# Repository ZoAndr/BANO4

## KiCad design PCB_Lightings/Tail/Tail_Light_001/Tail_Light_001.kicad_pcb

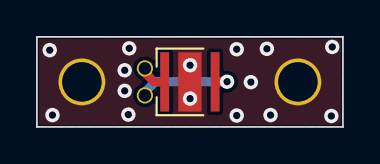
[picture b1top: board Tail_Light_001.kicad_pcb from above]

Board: 2 copper layers, 17.0 x 5.0 mm, 5 parts (0 on the bottom side), 3 nets.

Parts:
D1: LED_Cree_XHP50_6V; LED_Cree-XHP35
D2, D3: Conn_Hole_0p7; WireHole_0p7
U1, U2: Mounting_Hole_M2; Hole_screw_M2

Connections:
unnamed: D1.1 (K), D3.1
unnamed: D1.2 (A), D2.1
unnamed: D1.3 (PAD), U1.1 (Mnt), U2.1 (Mnt)

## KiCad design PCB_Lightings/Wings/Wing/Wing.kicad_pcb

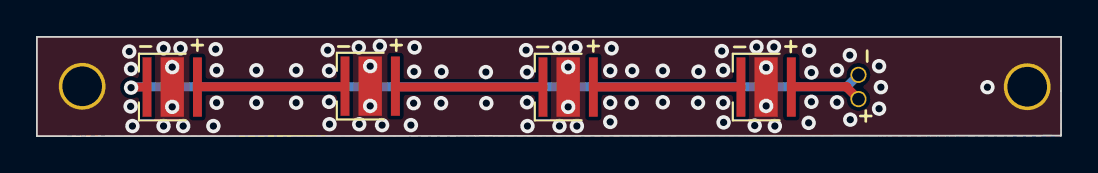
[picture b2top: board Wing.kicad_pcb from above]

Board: 2 copper layers, 56.9 x 5.5 mm, 8 parts (0 on the bottom side), 6 nets.

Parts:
D1, D2, D3, D4: LED_Cree_XHP50_6V; LED_Cree-XHP35
D5, D6: Conn_Hole_0p7; WireHole_0p7
U1, U2: Mounting_Hole_M2; Hole_screw_M2

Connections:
unnamed: D1.1 (K), D6.1
unnamed: D1.2 (A), D2.1 (K)
unnamed: D1.3 (PAD), D2.3 (PAD), D3.3 (PAD), D4.3 (PAD), U1.1 (Mnt), U2.1 (Mnt)
unnamed: D2.2 (A), D3.1 (K)
unnamed: D3.2 (A), D4.1 (K)
unnamed: D4.2 (A), D5.1

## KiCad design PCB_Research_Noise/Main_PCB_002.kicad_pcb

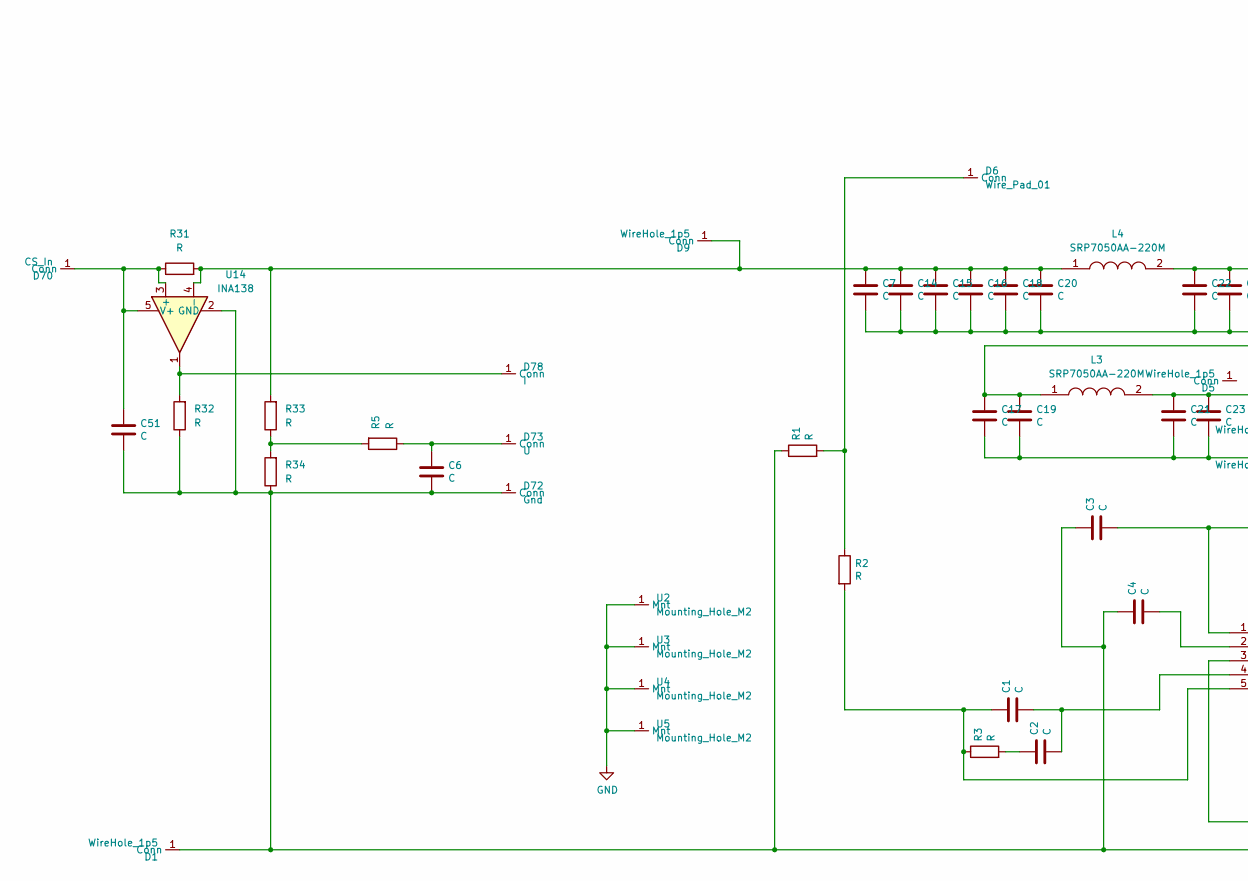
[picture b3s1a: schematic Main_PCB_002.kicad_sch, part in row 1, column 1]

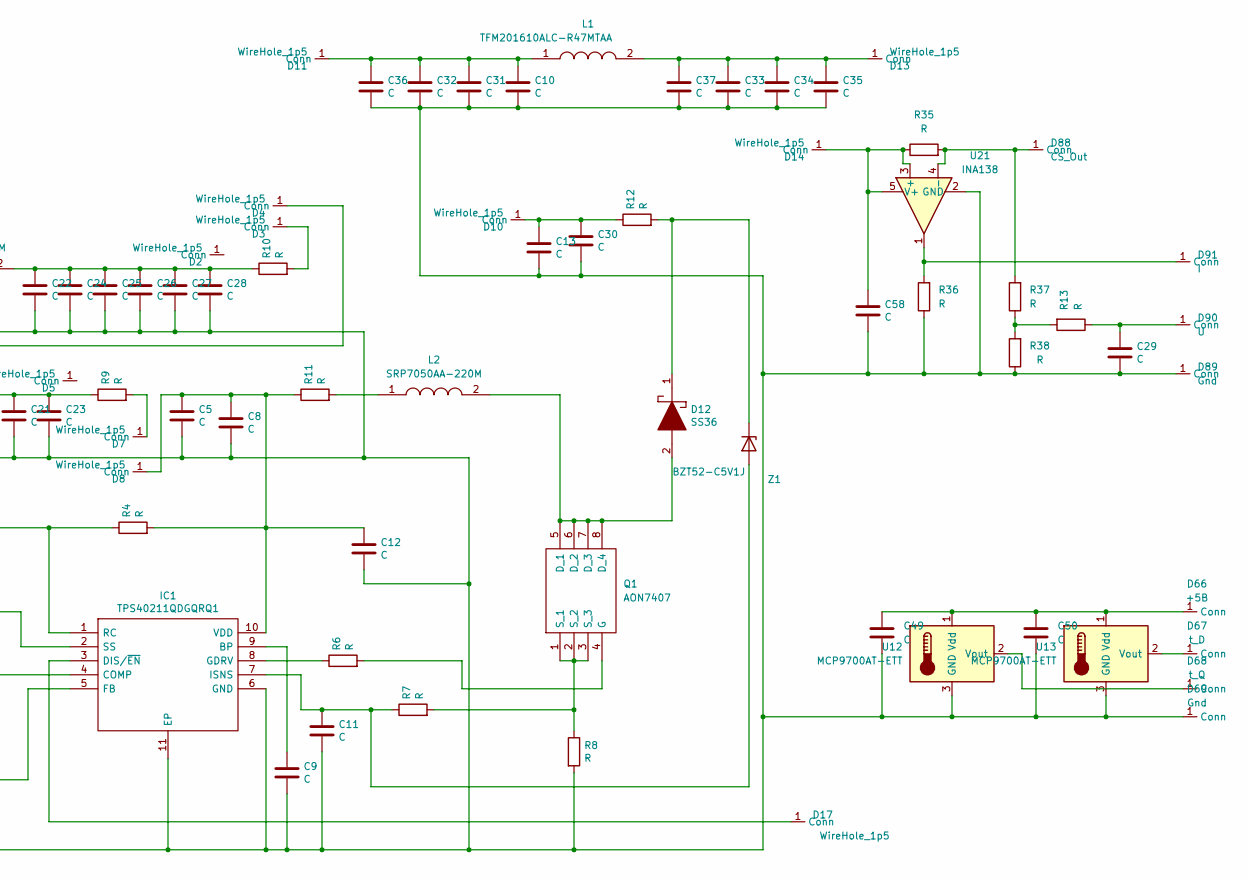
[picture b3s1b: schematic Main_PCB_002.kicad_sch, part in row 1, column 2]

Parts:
C1, C2, C3, C4, C5, C6, C8, C9, C10, C11, C14, C15, C16, C17, C18, C19, C20, C21, C22, C23, C24, C25, C26, C27, C29, C30, C31, C32, C33, C34, C35, C36, C37, C49, C50, C51, C58: C; C_0805_2012Metric_Pad1.18x1.45mm_HandSolder
C7, C12, C28: C; C_0603_1608Metric_Pad1.08x0.95mm_HandSolder
C13: C; C_1206_3216Metric_Pad1.33x1.80mm_HandSolder
D1, D2, D3, D4, D5, D7, D8, D9, D10, D11, D13, D14, D17: WireHole_1p5; WireHole_1p2
D6: Wire_Pad_01; Wire_Hole_1mm
D12: SS36; SODFL4626X120N; Manufacturer_Part_Number SS36
D66: +5B; WireHole_1p2
D67: t_D; WireHole_1p2
D68: t_Q; WireHole_1p2
D69: Gnd; WireHole_1p2
D70: CS_In; Wire_Hole_1mm
D72, D89: Gnd; Wire_Hole_1mm
D73, D90: U; Wire_Hole_1mm
D78, D91: I; Wire_Hole_1mm
D88: CS_Out; Wire_Hole_1mm
IC1: TPS40211QDGQRQ1; SOP50P490X110-11N; Manufacturer_Part_Number TPS40211QDGQRQ1; Mouser Part Number 595-TPS40211QDGQRQ1
L1: TFM201610ALC-R47MTAA; INDC2016X80N; Manufacturer_Part_Number TFM201610ALC-R47MTAA; Mouser Part Number 810-TFM201610ALCR47M
L2, L3, L4: SRP7050AA-220M; INDPM5752X300N; Manufacturer_Part_Number SRP7050AA-220M; Mouser Part Number 652-SRP7050AA-220M
Q1: AON7407; DFN_3X3_EP; Manufacturer_Part_Number AON7407
R1, R2, R3, R4, R5, R6, R7, R8, R9, R10, R11, R12, R13, R31, R32, R33, R34, R35, R36, R37, R38: R; R_0805_2012Metric_Pad1.20x1.40mm_HandSolder
U2, U3, U4, U5: Mounting_Hole_M2; Mounting_Wuerth_WA-SMST-2.7mm_H1mm_9774010951
U12, U13: MCP9700AT-ETT; SOT-23
U14, U21: INA138; SOT-23-5
Z1: BZT52-C5V1J; D_SOD-323F; Manufacturer_Part_Number BZT52-C5V1J; Mouser Part Number N/A

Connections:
GND: U2.1 (Mnt), U3.1 (Mnt), U4.1 (Mnt), U5.1 (Mnt)
unnamed: C2.1, R3.2
unnamed: C21.1, C23.1, L3.2, R9.1
unnamed: C22.1, C24.1, C25.1, C26.1, C27.1, C28.1, L4.2, R10.1
unnamed: C3.1, C4.1, C5.2, C6.2, C7.2, C8.2, C9.2, C10.2, C11.2, C12.2, C13.2, C14.2, C15.2, C16.2, C17.2, C18.2, C19.2, C20.2, C21.2, C22.2, C23.2, C24.2, C25.2, C26.2, C27.2, C28.2, C29.2, C30.2, C31.2, C32.2, C33.2, C34.2, C35.2, C36.2, C37.2, C49.2, C50.2, C51.2, C58.2, D1.1 (Conn), D69.1 (Conn), D72.1 (Conn), D89.1 (Conn), IC1.6 (GND), IC1.11 (EP), R1.1, R8.2, R32.1, R34.1, R36.1, R38.1, U12.3 (GND), U13.3 (GND), U14.2 (GND), U21.2 (GND)
unnamed: D3.1 (Conn), R10.2
unnamed: C17.1, C19.1, D4.1 (Conn), L3.1
unnamed: D6.1 (Conn), R1.2, R2.1
unnamed: D7.1 (Conn), R9.2
unnamed: C5.1, C8.1, C12.1, D8.1 (Conn), IC1.10 (VDD), R4.2, R11.1
unnamed: C7.1, C14.1, C15.1, C16.1, C18.1, C20.1, D9.1 (Conn), L4.1, R31.2, R33.2, U14.4 (-)
unnamed: C13.1, C30.1, D10.1 (Conn), R12.1
unnamed: C10.1, C31.1, C32.1, C36.1, D11.1 (Conn), L1.1
unnamed: C33.1, C34.1, C35.1, C37.1, D13.1 (Conn), L1.2
unnamed: C58.1, D14.1 (Conn), R35.1, U21.3 (+), U21.5 (V+)
unnamed: D17.1 (Conn), IC1.3 (DIS/~EN)
unnamed: C49.1, C50.1, D66.1 (Conn), U12.1 (Vdd), U13.1 (Vdd)
unnamed: D67.1 (Conn), U13.2 (Vout)
unnamed: D68.1 (Conn), U12.2 (Vout)
unnamed: C51.1, D70.1 (Conn), R31.1, U14.3 (+), U14.5 (V+)
unnamed: C6.1, D73.1 (Conn), R5.1
unnamed: D78.1 (Conn), R32.2, U14.1
unnamed: D88.1 (Conn), R35.2, R37.2, U21.4 (-)
unnamed: C29.1, D90.1 (Conn), R13.1
unnamed: D91.1 (Conn), R36.2, U21.1
unnamed: C9.1, IC1.9 (BP)
unnamed: C1.2, C2.2, IC1.4 (COMP)
unnamed: C1.1, IC1.5 (FB), R2.2, R3.1
unnamed: IC1.8 (GDRV), R6.1
unnamed: C11.1, IC1.7 (ISNS), R7.1, Z1.2 (A)
unnamed: C3.2, IC1.1 (RC), R4.1
unnamed: C4.2, IC1.2 (SS)
unnamed: L2.1, R11.2
unnamed: D12.2, L2.2, Q1.5 (D_1), Q1.6 (D_2), Q1.7 (D_3), Q1.8 (D_4)
unnamed: Q1.4 (G), R6.2
unnamed: Q1.1 (S_1), Q1.2 (S_2), Q1.3 (S_3), R7.2, R8.1
unnamed: R13.2, R37.1, R38.2
unnamed: R5.2, R33.1, R34.2
unnamed: D12.1, R12.2, Z1.1 (K)

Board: 2 copper layers, 104 parts (0 on the bottom side), 39 nets, no tracks yet.
